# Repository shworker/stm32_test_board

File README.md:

# stm32_test_board
STM32 MCU test &amp; development board with ZIF panel for MCUs in QFP48 package
Contains project in KiCAD 6 format, PDF for schematic & board and gerber files

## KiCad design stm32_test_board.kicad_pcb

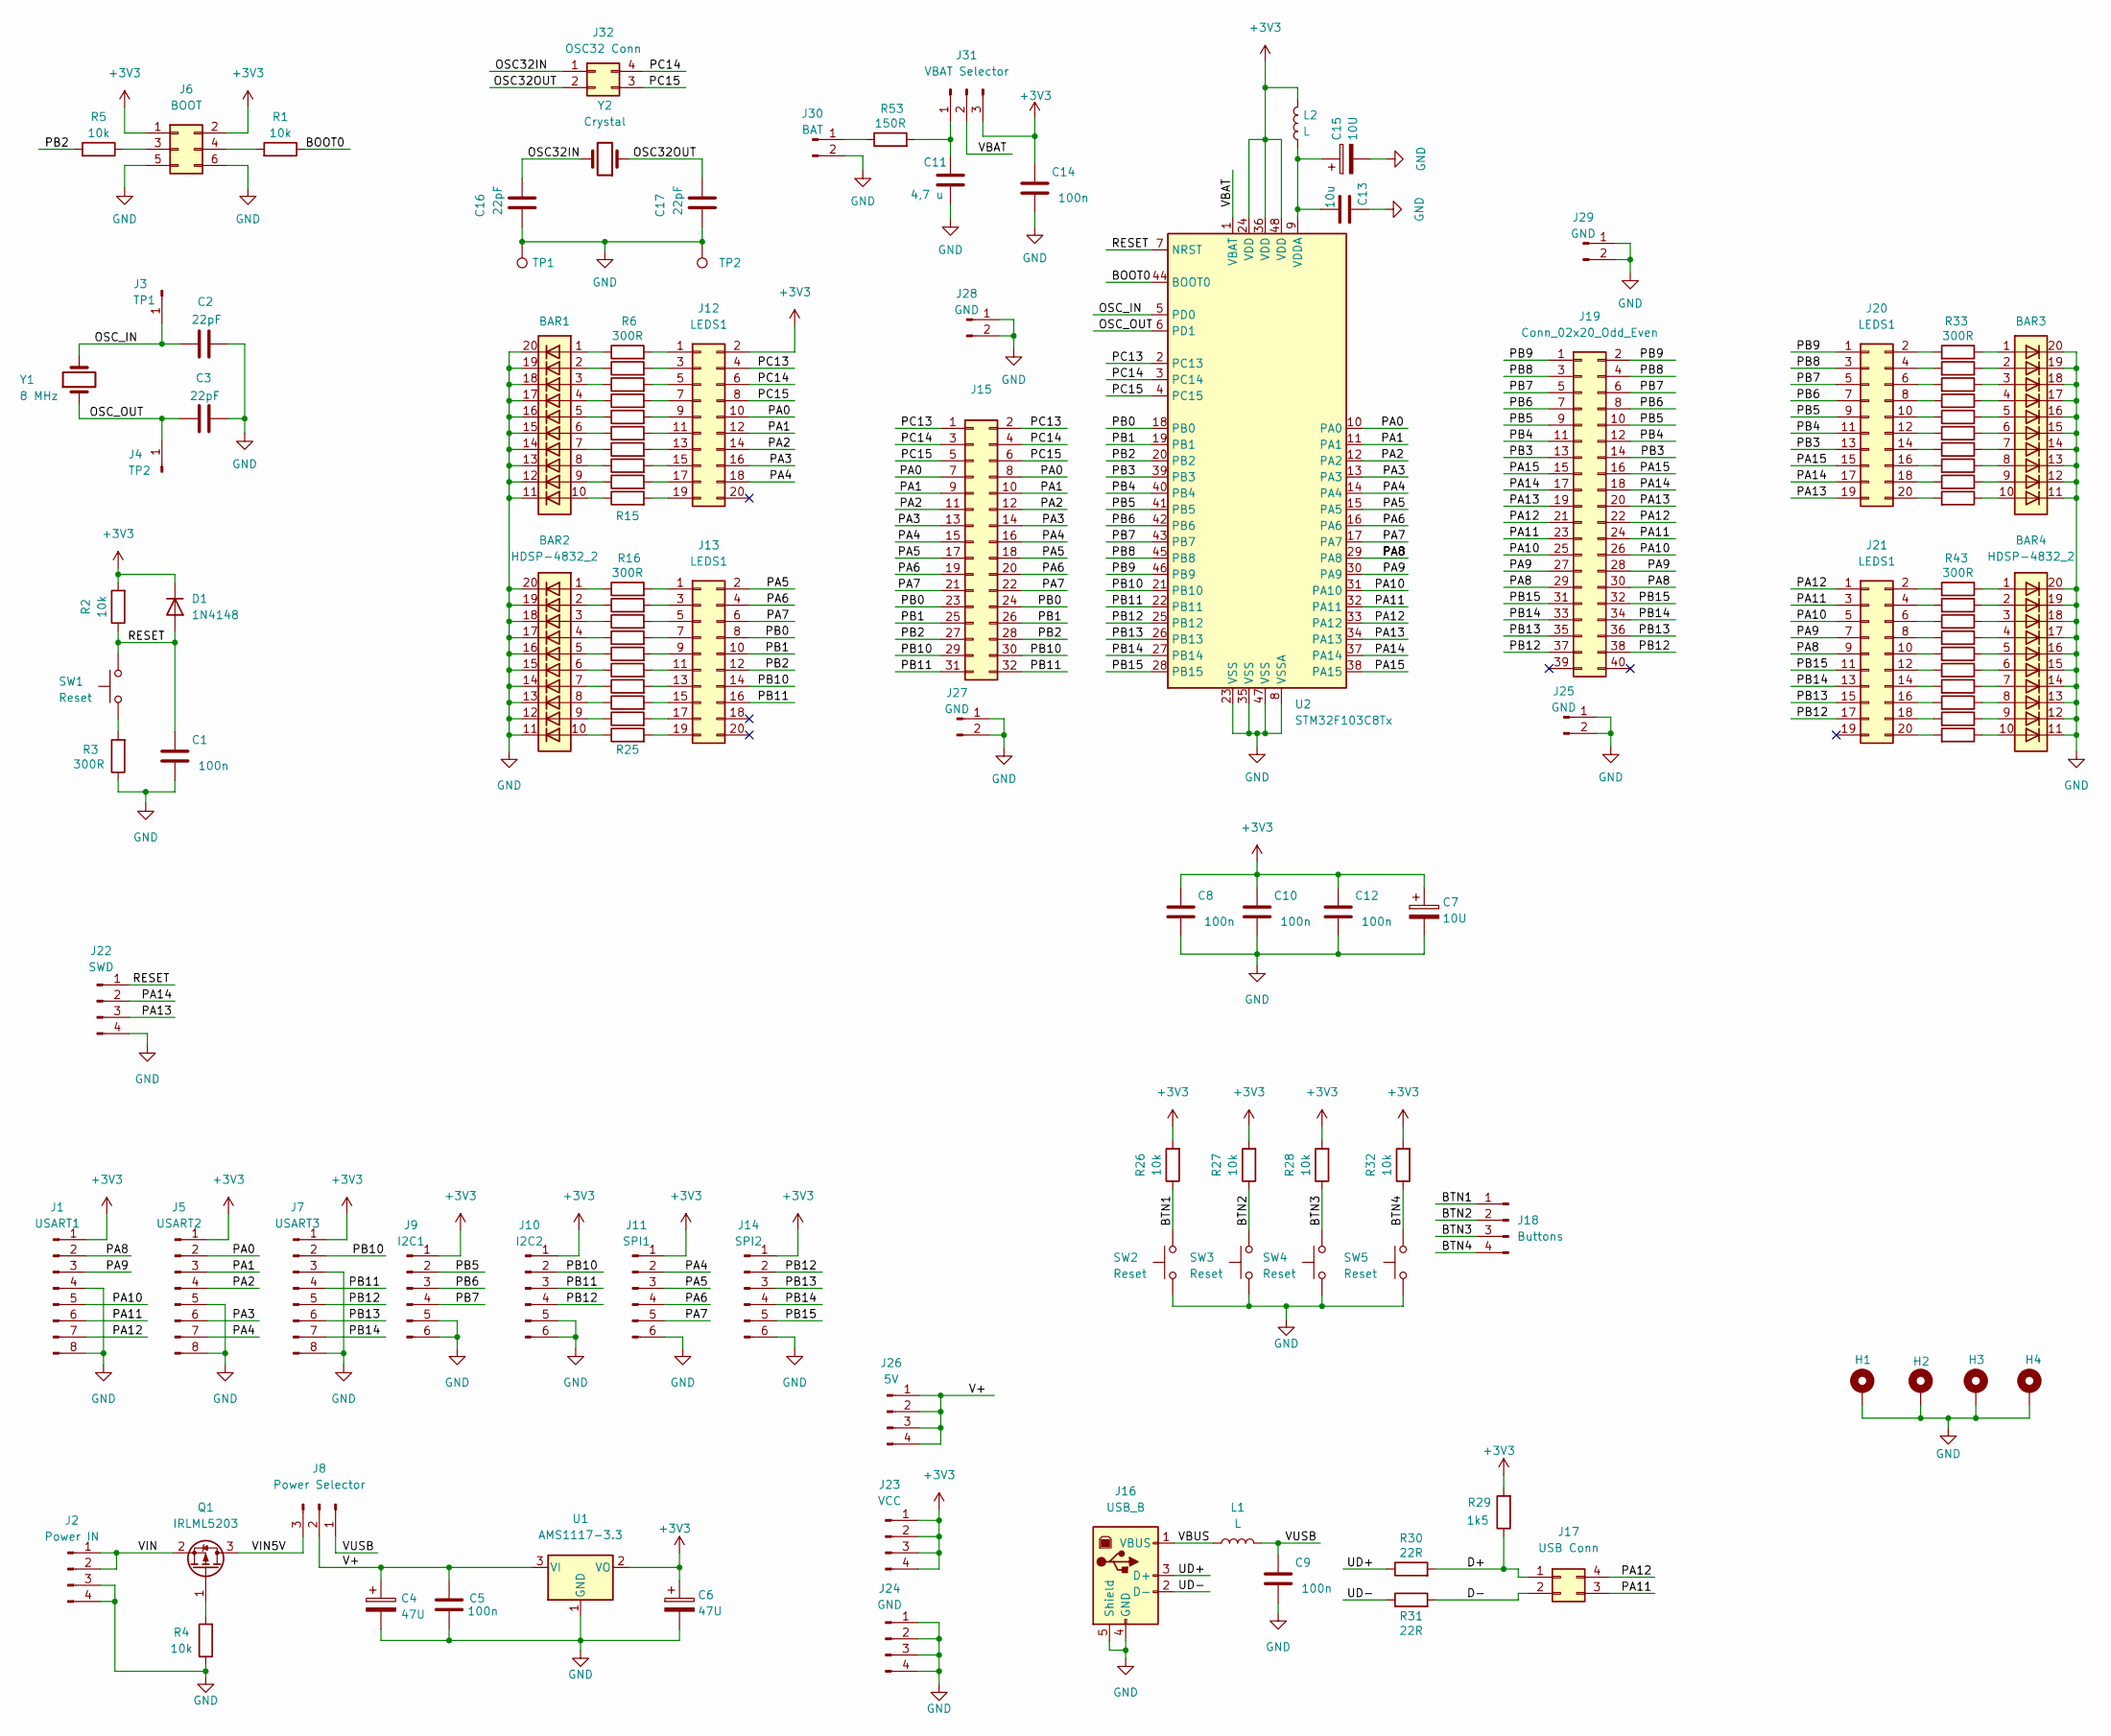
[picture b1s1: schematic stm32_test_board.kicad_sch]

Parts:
BAR1, BAR2, BAR3, BAR4: HDSP-4832_2; DC10EWA
C1, C5, C8, C9, C10, C12, C14: 100n; C_0603_1608Metric_Pad1.08x0.95mm_HandSolder
C2, C3, C16, C17: 22pF; C_0603_1608Metric_Pad1.08x0.95mm_HandSolder
C4, C6: 47U; CP_Radial_D5.0mm_P2.00mm
C7: 10U; CP_EIA-3528-21_Kemet-B_Pad1.50x2.35mm_HandSolder
C11: 4,7 u; CP_EIA-3216-18_Kemet-A_Pad1.58x1.35mm_HandSolder
C13: 10u; C_0603_1608Metric_Pad1.08x0.95mm_HandSolder
C15: 10U; CP_EIA-3216-18_Kemet-A_Pad1.58x1.35mm_HandSolder
D1: 1N4148; D_5W_P12.70mm_Horizontal
H1, H2, H3, H4: MountingHole_Pad; MountingHole_3.2mm_M3_DIN965_Pad
J1: USART1; PinHeader_1x08_P2.54mm_Vertical
J2: Power IN; PinHeader_1x04_P2.54mm_Vertical
J3: TP1; PinHeader_1x01_P2.54mm_Vertical
J4: TP2; PinHeader_1x01_P2.54mm_Vertical
J5: USART2; PinHeader_1x08_P2.54mm_Vertical
J6: BOOT; PinHeader_2x03_P2.54mm_Vertical
J7: USART3; PinHeader_1x08_P2.54mm_Vertical
J8: Power Selector; PinHeader_1x03_P2.54mm_Vertical
J9: I2C1; PinHeader_1x06_P2.54mm_Vertical
J10: I2C2; PinHeader_1x06_P2.54mm_Vertical
J11: SPI1; PinHeader_1x06_P2.54mm_Vertical
J12, J13, J20, J21: LEDS1; PinHeader_2x10_P2.54mm_Vertical
J14: SPI2; PinHeader_1x06_P2.54mm_Vertical
J15: Conn_02x16_Odd_Even; PinHeader_2x16_P2.54mm_Vertical
J16: USB_B; USB_B_Lumberg_2411_02_Horizontal
J17: USB Conn; PinHeader_2x02_P2.54mm_Vertical
J18: Buttons; PinHeader_1x04_P2.54mm_Vertical
J19: Conn_02x20_Odd_Even; PinHeader_2x20_P2.54mm_Vertical
J22: SWD; PinHeader_1x04_P2.54mm_Vertical
J23: VCC; PinHeader_1x04_P2.54mm_Vertical
J24: GND; PinHeader_1x04_P2.54mm_Vertical
J25, J27, J28, J29: GND; PinHeader_1x02_P2.54mm_Vertical
J26: 5V; PinHeader_1x04_P2.54mm_Vertical
J30: BAT; PinHeader_1x02_P2.54mm_Vertical
J31: VBAT Selector; PinHeader_1x03_P2.54mm_Vertical
J32: OSC32 Conn; PinHeader_2x02_P2.54mm_Vertical
L1, L2: L; L_0603_1608Metric_Pad1.05x0.95mm_HandSolder
Q1: IRLML5203; SOT-23
R1, R2, R4, R5, R26, R27, R28, R32: 10k; R_0603_1608Metric_Pad0.98x0.95mm_HandSolder
R3, R6, R7, R8, R9, R10, R11, R12, R13, R14, R15, R16, R17, R18, R19, R20, R21, R22, R23, R24, R25, R33, R34, R35, R36, R37, R38, R39, R40, R41, R42, R43, R44, R45, R46, R47, R48, R49, R50, R51, R52: 300R; R_0603_1608Metric_Pad0.98x0.95mm_HandSolder
R29: 1k5; R_0603_1608Metric_Pad0.98x0.95mm_HandSolder
R30, R31: 22R; R_0603_1608Metric_Pad0.98x0.95mm_HandSolder
R53: 150R; R_0603_1608Metric_Pad0.98x0.95mm_HandSolder
SW1, SW2, SW3, SW4, SW5: Reset; SW_PUSH_6mm
TP1, TP2: TestPoint; TestPoint_THTPad_1.0x1.0mm_Drill0.5mm
U1: AMS1117-3.3; SOT-223-3_TabPin2
U2: STM32F103C8Tx; DIP-48-W16.51
Y1: 8 MHz; Crystal_HC49-4H_Vertical
Y2: Crystal; Crystal_C26-LF_D2.1mm_L6.5mm_Horizontal

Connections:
+3V3: C6.1, C7.1, C8.1, C10.1, C12.1, C14.1, D1.1 (K), J1.1, J5.1, J6.1, J6.2, J7.1, J9.1, J10.1, J11.1, J12.2, J14.1, J23.1, J23.2, J23.3, J23.4, J31.3, L2.2, R2.2, R26.2, R27.2, R28.2, R29.2, R32.2, U1.2 (VO), U2.24 (VDD), U2.36 (VDD), U2.48 (VDD)
/BOOT0: R1.1, U2.44 (BOOT0)
/BTN1: J18.1, R26.1, SW2.2
/BTN2: J18.2, R27.1, SW3.2
/BTN3: J18.3, R28.1, SW4.2
/BTN4: J18.4, R32.1, SW5.2
/D+: J17.1, R29.1, R30.2
/D-: J17.2, R31.2
/OSC32IN: C16.2, J32.1, Y2.2
/OSC32OUT: C17.2, J32.2, Y2.1
/OSC_IN: C2.1, J3.1, U2.5 (PD0), Y1.2
/OSC_OUT: C3.1, J4.1, U2.6 (PD1), Y1.1
/PA0: J5.2, J12.10, J15.7, J15.8, U2.10 (PA0)
/PA1: J5.3, J12.12, J15.9, J15.10, U2.11 (PA1)
/PA2: J5.4, J12.14, J15.11, J15.12, U2.12 (PA2)
/PA3: J5.6, J12.16, J15.13, J15.14, U2.13 (PA3)
/PA4: J5.7, J11.2, J12.18, J15.15, J15.16, U2.14 (PA4)
/PA5: J11.3, J13.2, J15.17, J15.18, U2.15 (PA5)
/PA6: J11.4, J13.4, J15.19, J15.20, U2.16 (PA6)
/PA7: J11.5, J13.6, J15.21, J15.22, U2.17 (PA7)
/PA8: J1.2, J19.29, J19.30, J21.9, U2.29 (PA8)
/PA9: J1.3, J19.27, J19.28, J21.7, U2.30 (PA9)
/PA10: J1.5, J19.25, J19.26, J21.5, U2.31 (PA10)
/PA11: J1.6, J17.3, J19.23, J19.24, J21.3, U2.32 (PA11)
/PA12: J1.7, J17.4, J19.21, J19.22, J21.1, U2.33 (PA12)
/PA13: J19.19, J19.20, J20.19, J22.3, U2.34 (PA13)
/PA14: J19.17, J19.18, J20.17, J22.2, U2.37 (PA14)
/PA15: J19.15, J19.16, J20.15, U2.38 (PA15)
/PB0: J13.8, J15.23, J15.24, U2.18 (PB0)
/PB1: J13.10, J15.25, J15.26, U2.19 (PB1)
/PB2: J13.12, J15.27, J15.28, R5.2, U2.20 (PB2)
/PB3: J19.13, J19.14, J20.13, U2.39 (PB3)
/PB4: J19.11, J19.12, J20.11, U2.40 (PB4)
/PB5: J9.2, J19.9, J19.10, J20.9, U2.41 (PB5)
/PB6: J9.3, J19.7, J19.8, J20.7, U2.42 (PB6)
/PB7: J9.4, J19.5, J19.6, J20.5, U2.43 (PB7)
/PB8: J19.3, J19.4, J20.3, U2.45 (PB8)
/PB9: J19.1, J19.2, J20.1, U2.46 (PB9)
/PB10: J7.2, J10.2, J13.14, J15.29, J15.30, U2.21 (PB10)
/PB11: J7.4, J10.3, J13.16, J15.31, J15.32, U2.22 (PB11)
/PB12: J7.5, J10.4, J14.2, J19.37, J19.38, J21.17, U2.25 (PB12)
/PB13: J7.6, J14.3, J19.35, J19.36, J21.15, U2.26 (PB13)
/PB14: J7.7, J14.4, J19.33, J19.34, J21.13, U2.27 (PB14)
/PB15: J14.5, J19.31, J19.32, J21.11, U2.28 (PB15)
/PC13: J12.4, J15.1, J15.2, U2.2 (PC13)
/PC14: J12.6, J15.3, J15.4, J32.4, U2.3 (PC14)
/PC15: J12.8, J15.5, J15.6, J32.3, U2.4 (PC15)
/RESET: C1.1, D1.2 (A), J22.1, R2.1, SW1.2, U2.7 (NRST)
/UD+: J16.3 (D+), R30.1
/UD-: J16.2 (D-), R31.1
/V+: C4.1, C5.1, J8.2, J26.1, J26.2, J26.3, J26.4, U1.3 (VI)
/VBAT: J31.2, U2.1 (VBAT)
/VBUS: J16.1 (VBUS), L1.1
/VIN: J2.1, J2.2, Q1.2 (S)
/VIN5V: J8.3, Q1.3 (D)
/VUSB: C9.1, J8.1, L1.2
GND: BAR1.11 (K), BAR1.12 (K), BAR1.13 (K), BAR1.14 (K), BAR1.15 (K), BAR1.16 (K), BAR1.17 (K), BAR1.18 (K), BAR1.19 (K), BAR1.20 (K), BAR2.11 (K), BAR2.12 (K), BAR2.13 (K), BAR2.14 (K), BAR2.15 (K), BAR2.16 (K), BAR2.17 (K), BAR2.18 (K), BAR2.19 (K), BAR2.20 (K), BAR3.11 (K), BAR3.12 (K), BAR3.13 (K), BAR3.14 (K), BAR3.15 (K), BAR3.16 (K), BAR3.17 (K), BAR3.18 (K), BAR3.19 (K), BAR3.20 (K), BAR4.11 (K), BAR4.12 (K), BAR4.13 (K), BAR4.14 (K), BAR4.15 (K), BAR4.16 (K), BAR4.17 (K), BAR4.18 (K), BAR4.19 (K), BAR4.20 (K), C1.2, C2.2, C3.2, C4.2, C5.2, C6.2, C7.2, C8.2, C9.2, C10.2, C11.2, C12.2, C13.1, C14.2, C15.2, C16.1, C17.1, H1.1, H2.1, H3.1, H4.1, J1.4, J1.8, J2.3, J2.4, J5.5, J5.8, J6.5, J6.6, J7.3, J7.8, J9.5, J9.6, J10.5, J10.6, J11.6, J14.6, J16.4 (GND), J16.5 (Shield), J22.4, J24.1, J24.2, J24.3, J24.4, J25.1, J25.2, J27.1, J27.2, J28.1, J28.2, J29.1, J29.2, J30.2, R3.1, R4.1, SW2.1, SW3.1, SW4.1, SW5.1, TP1.1, TP2.1, U1.1 (GND), U2.8 (VSSA), U2.23 (VSS), U2.35 (VSS), U2.47 (VSS)
unnamed: BAR1.1 (A), R6.1
unnamed: BAR1.2 (A), R7.1
unnamed: BAR1.3 (A), R8.1
unnamed: BAR1.4 (A), R9.1
unnamed: BAR1.5 (A), R10.1
unnamed: BAR1.6 (A), R11.1
unnamed: BAR1.7 (A), R12.1
unnamed: BAR1.8 (A), R13.1
unnamed: BAR1.9 (A), R14.1
unnamed: BAR1.10 (A), R15.1
unnamed: BAR2.1 (A), R16.1
unnamed: BAR2.2 (A), R17.1
unnamed: BAR2.3 (A), R18.1
unnamed: BAR2.4 (A), R19.1
unnamed: BAR2.5 (A), R20.1
unnamed: BAR2.6 (A), R21.1
unnamed: BAR2.7 (A), R22.1
unnamed: BAR2.8 (A), R23.1
unnamed: BAR2.9 (A), R24.1
unnamed: BAR2.10 (A), R25.1
unnamed: BAR3.1 (A), R33.1
unnamed: BAR3.2 (A), R34.1
unnamed: BAR3.3 (A), R35.1
unnamed: BAR3.4 (A), R36.1
unnamed: BAR3.5 (A), R37.1
unnamed: BAR3.6 (A), R38.1
unnamed: BAR3.7 (A), R39.1
unnamed: BAR3.8 (A), R40.1
unnamed: BAR3.9 (A), R41.1
unnamed: BAR3.10 (A), R42.1
unnamed: BAR4.1 (A), R43.1
unnamed: BAR4.2 (A), R44.1
unnamed: BAR4.3 (A), R45.1
unnamed: BAR4.4 (A), R46.1
unnamed: BAR4.5 (A), R47.1
unnamed: BAR4.6 (A), R48.1
unnamed: BAR4.7 (A), R49.1
unnamed: BAR4.8 (A), R50.1
unnamed: BAR4.9 (A), R51.1
unnamed: BAR4.10 (A), R52.1
unnamed: C11.1, J31.1, R53.2
unnamed: C13.2, C15.1, L2.1, U2.9 (VDDA)
unnamed: J6.3, R5.1
unnamed: J6.4, R1.2
unnamed: J12.1, R6.2
unnamed: J12.3, R7.2
unnamed: J12.5, R8.2
unnamed: J12.7, R9.2
unnamed: J12.9, R10.2
unnamed: J12.11, R11.2
unnamed: J12.13, R12.2
unnamed: J12.15, R13.2
unnamed: J12.17, R14.2
unnamed: J12.19, R15.2
unnamed: J13.1, R16.2
unnamed: J13.3, R17.2
unnamed: J13.5, R18.2
unnamed: J13.7, R19.2
unnamed: J13.9, R20.2
unnamed: J13.11, R21.2
unnamed: J13.13, R22.2
unnamed: J13.15, R23.2
unnamed: J13.17, R24.2
unnamed: J13.19, R25.2
unnamed: J20.2, R33.2
unnamed: J20.4, R34.2
unnamed: J20.6, R35.2
unnamed: J20.8, R36.2
unnamed: J20.10, R37.2
unnamed: J20.12, R38.2
unnamed: J20.14, R39.2
unnamed: J20.16, R40.2
unnamed: J20.18, R41.2
unnamed: J20.20, R42.2
unnamed: J21.2, R43.2
unnamed: J21.4, R44.2
unnamed: J21.6, R45.2
unnamed: J21.8, R46.2
unnamed: J21.10, R47.2
unnamed: J21.12, R48.2
unnamed: J21.14, R49.2
unnamed: J21.16, R50.2
unnamed: J21.18, R51.2
unnamed: J21.20, R52.2
unnamed: J30.1, R53.1
unnamed: Q1.1 (G), R4.2
unnamed: R3.2, SW1.1

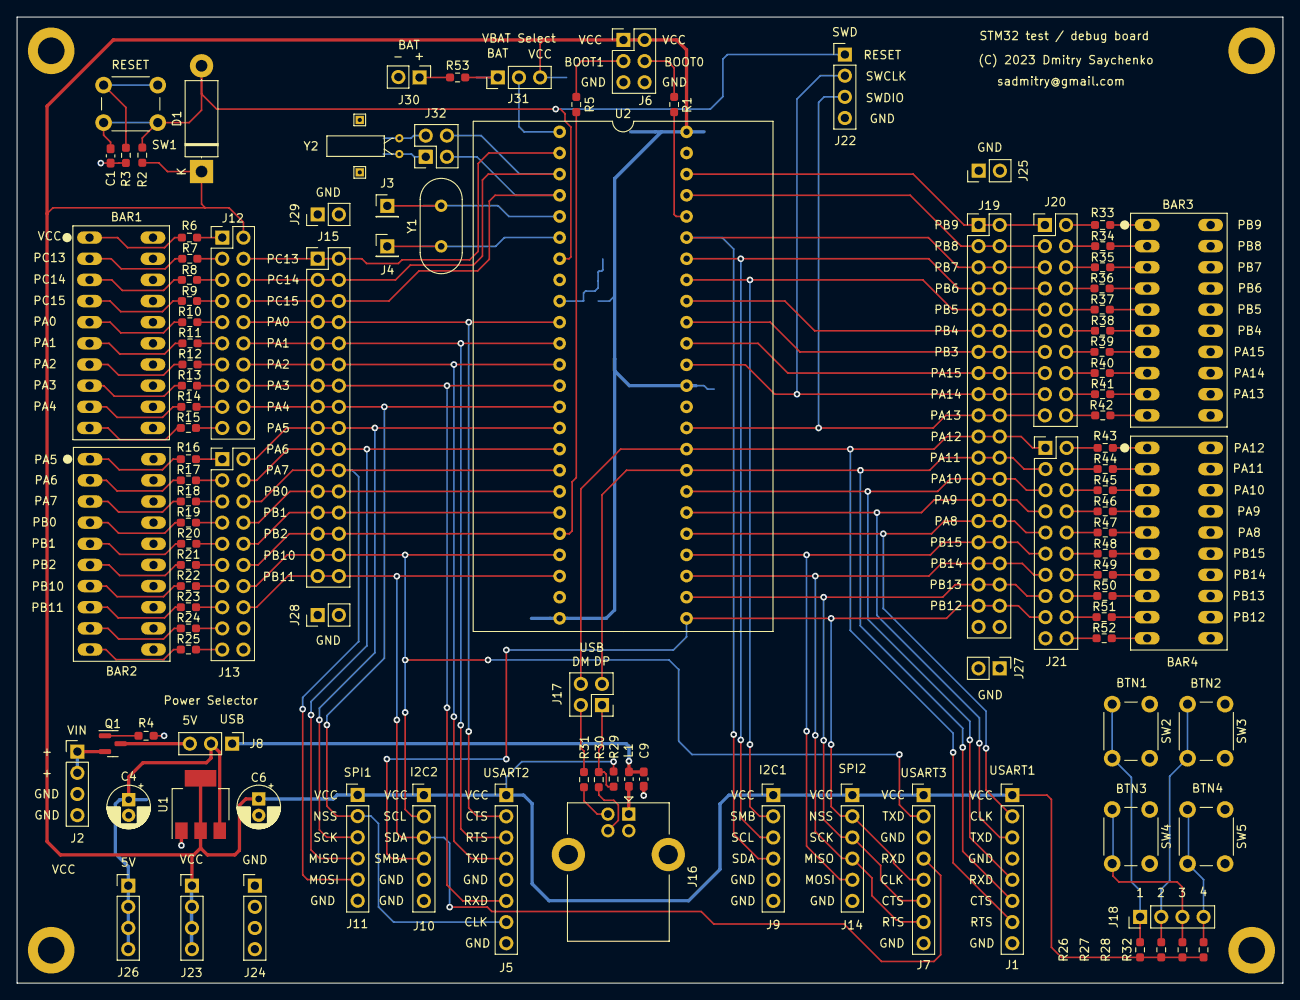
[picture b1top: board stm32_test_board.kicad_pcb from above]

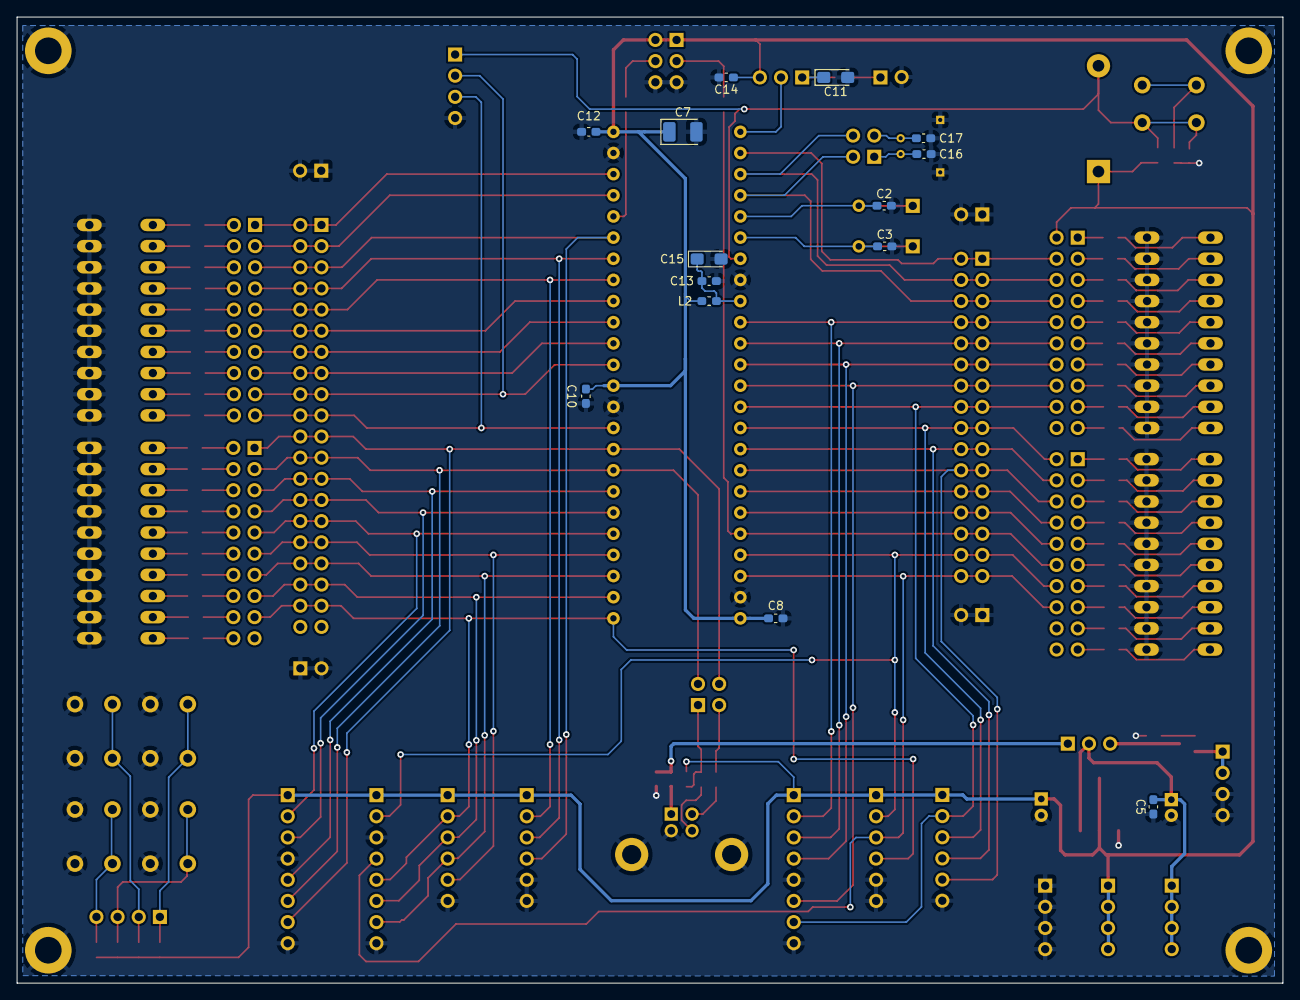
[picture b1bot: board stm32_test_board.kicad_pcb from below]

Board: 2 copper layers, 152.0 x 116.0 mm, 125 parts (14 on the bottom side), 144 nets.

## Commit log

2023-11-24 Update README.md
    Add some text
2023-12-04 Fix some errors

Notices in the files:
stm32_test_board.kicad_pcb:
(C) 2023 Dmitry Saychenko
